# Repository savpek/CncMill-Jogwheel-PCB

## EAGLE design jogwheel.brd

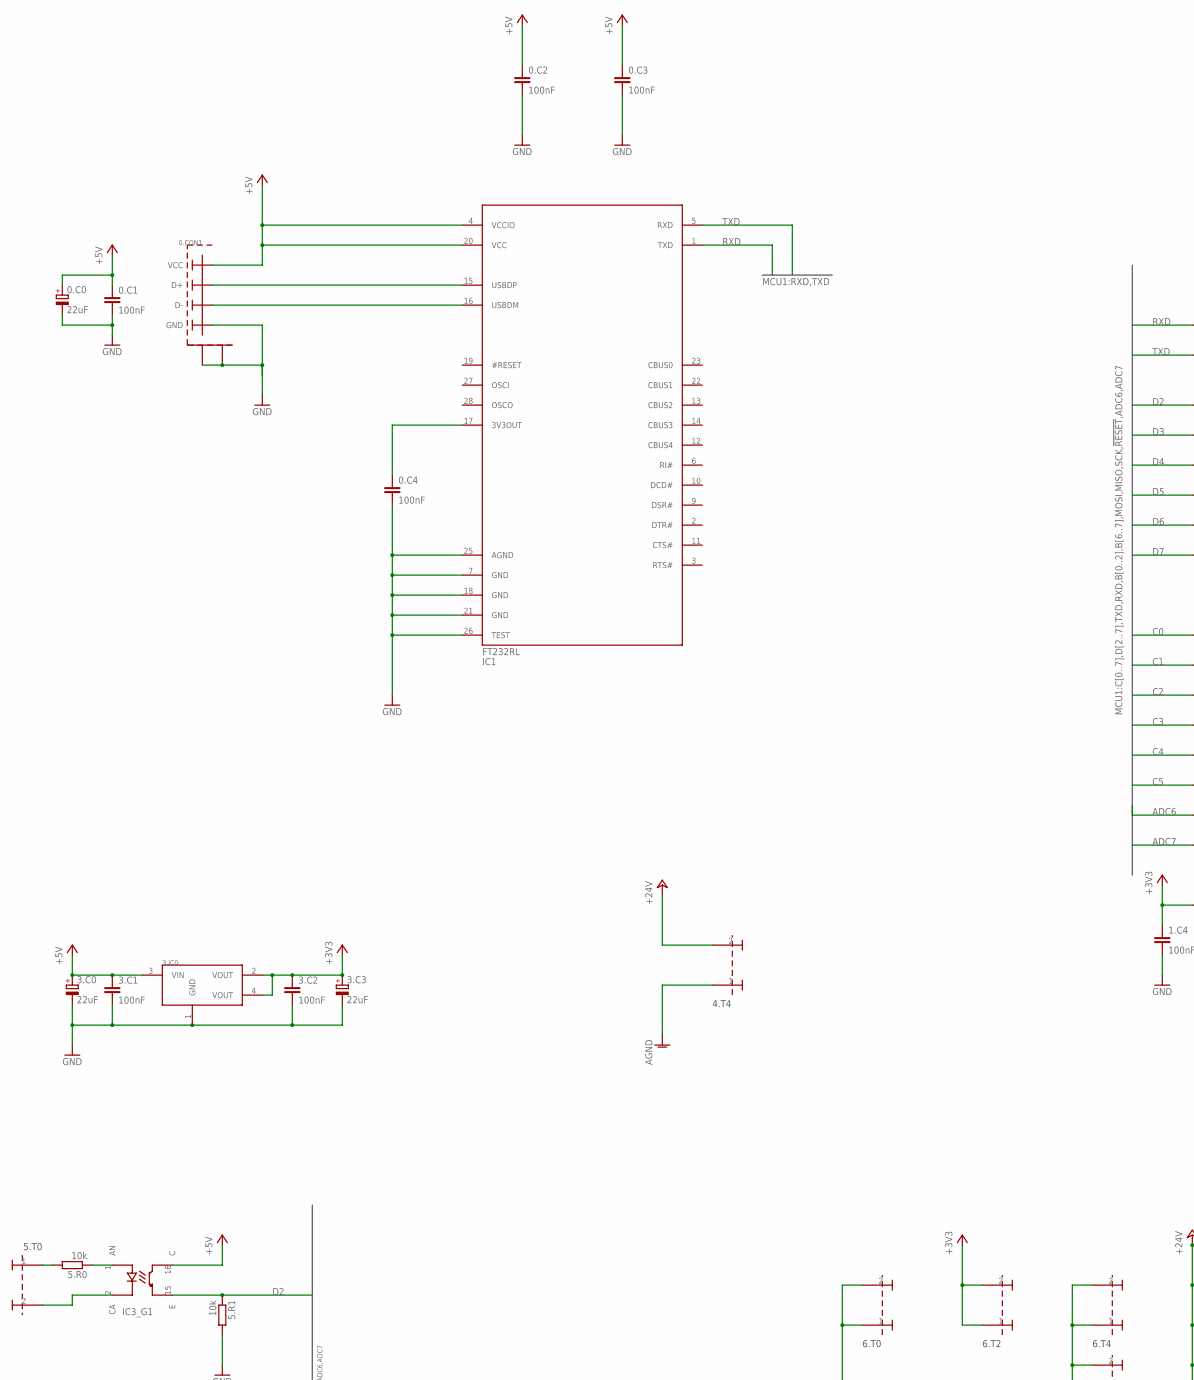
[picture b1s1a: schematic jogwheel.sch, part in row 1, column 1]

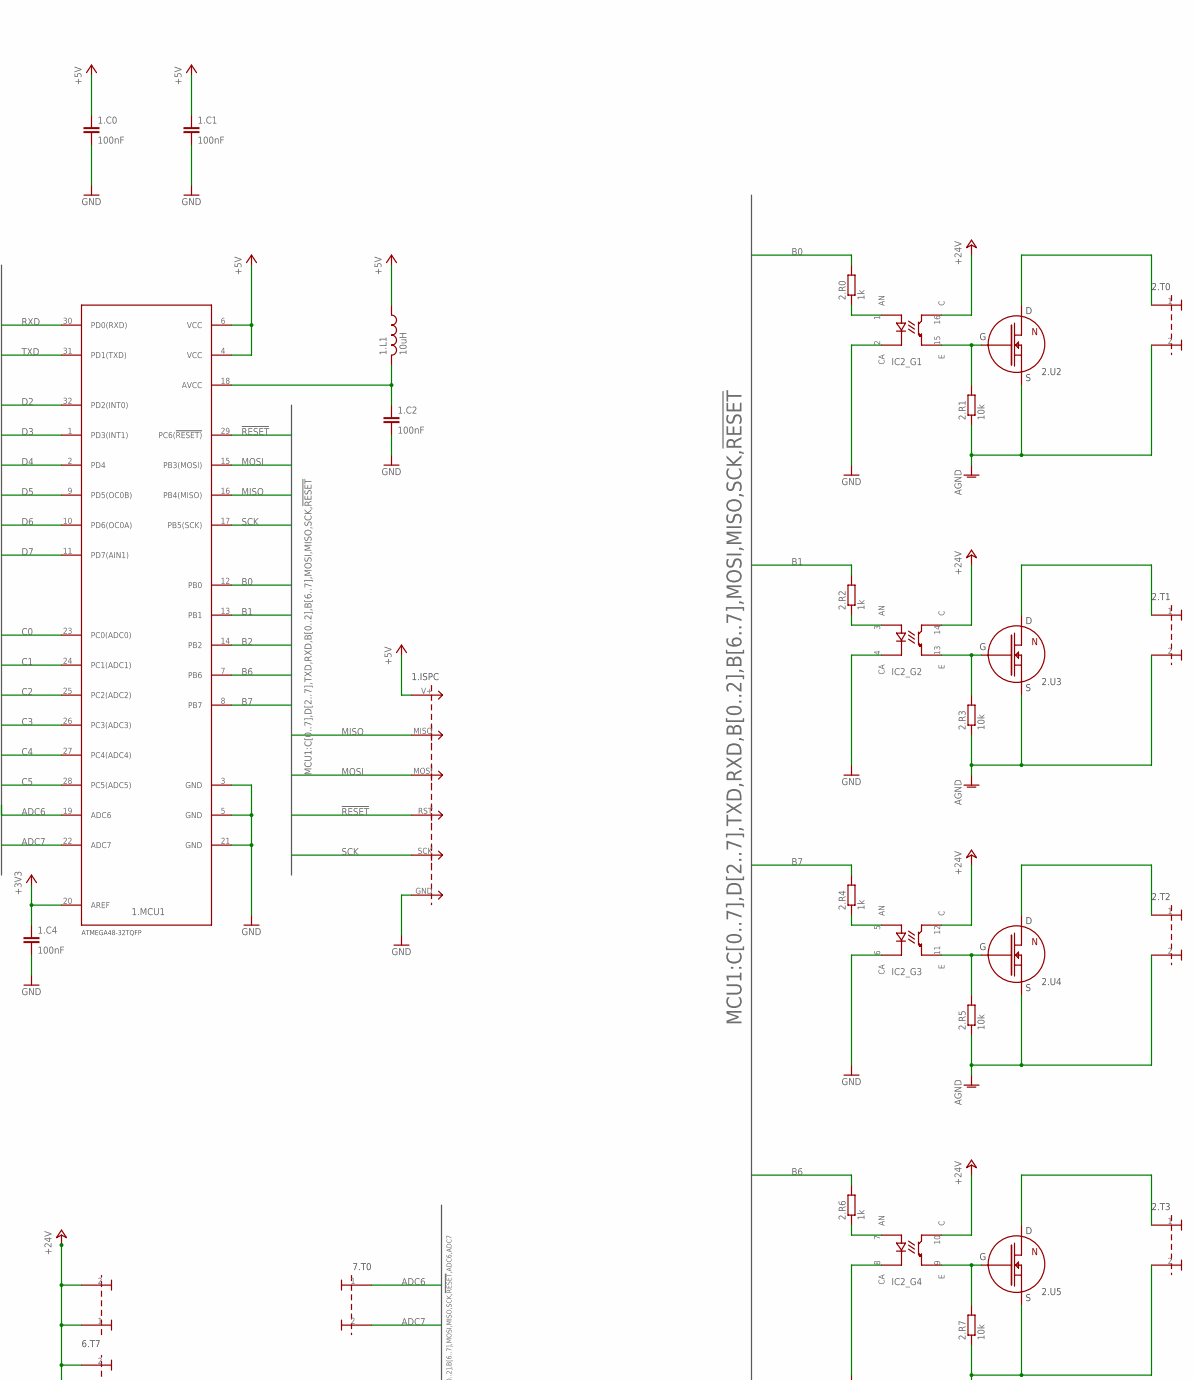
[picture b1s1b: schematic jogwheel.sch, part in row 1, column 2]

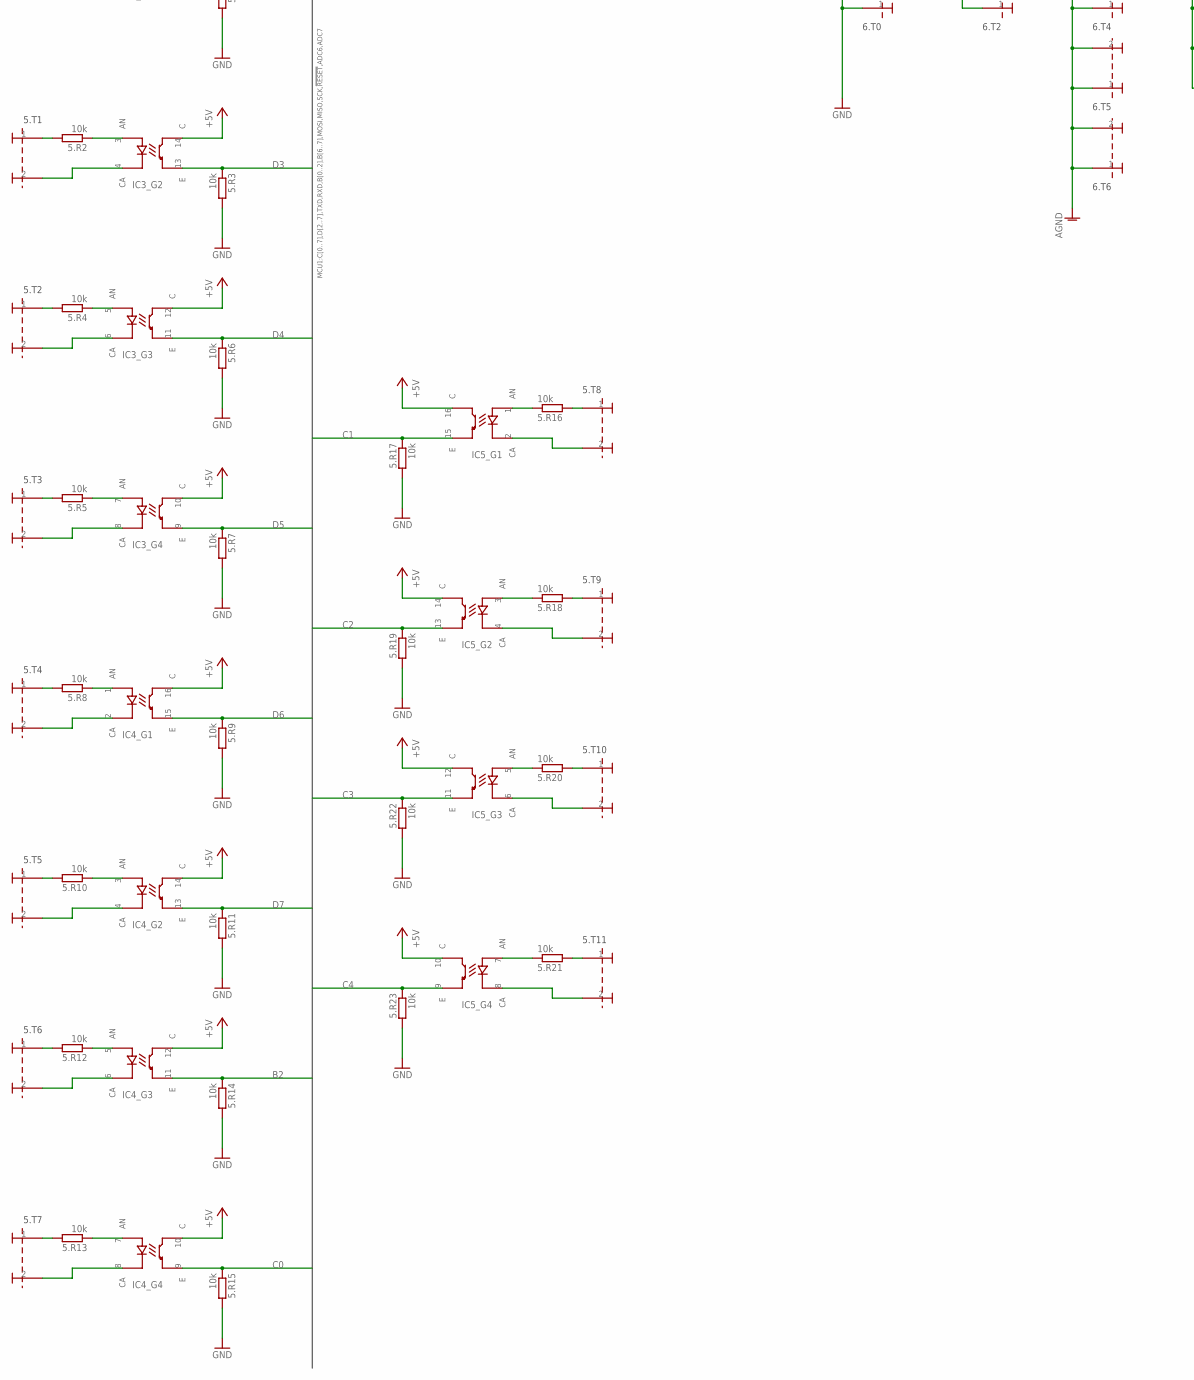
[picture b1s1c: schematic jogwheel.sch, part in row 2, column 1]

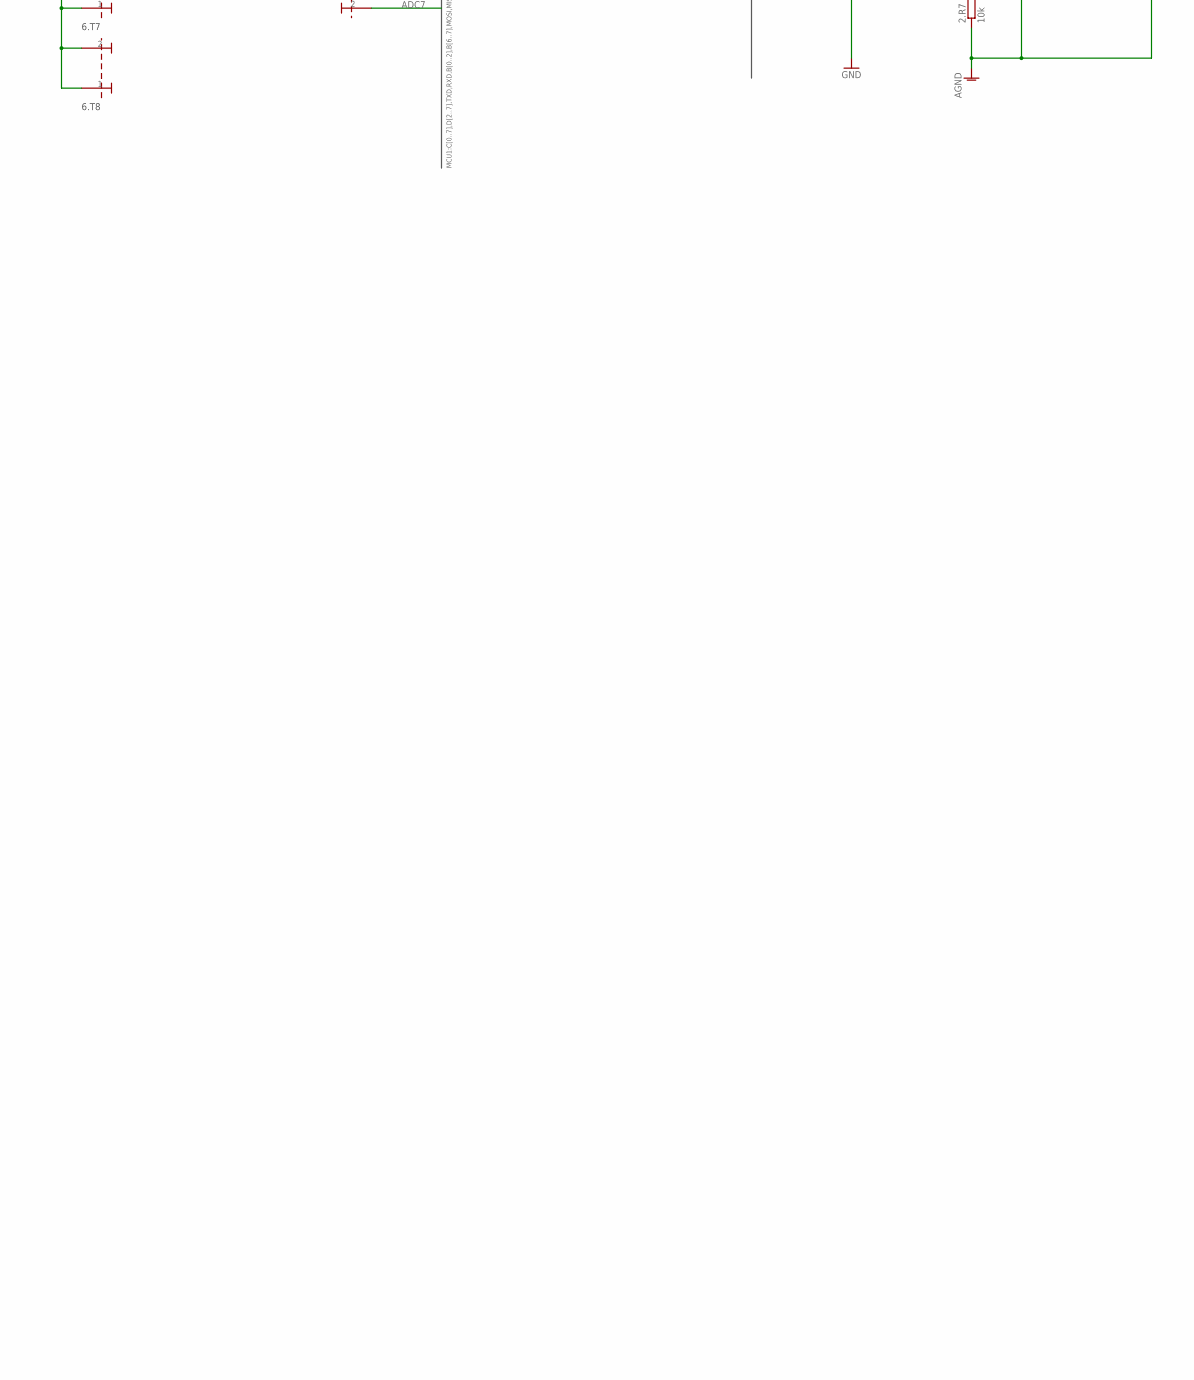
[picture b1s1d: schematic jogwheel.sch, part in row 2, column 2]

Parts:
0.C0, 3.C0, 3.C3: 22uF; E1.5-5
0.C1, 0.C2, 0.C3, 0.C4, 1.C0, 1.C1, 1.C2, 1.C4, 3.C1, 3.C2: 100nF; C0805
0.CON1: USB-BWUERTH-ELECTRONIC-USB-B; USB-B-THROUGH-HOLE
1.ISPC: CONNECTOR_6PIN2X3_ISP; 2X3_ISP
1.L1: 10uH; C0805
1.MCU1: ATMEGA48-20PU-32TQFPTQFP32; TQFP32-08
2.R0, 2.R2, 2.R4, 2.R6: 1k; R0805
2.R1, 2.R3, 2.R5, 2.R7, 5.R0, 5.R1, 5.R2, 5.R3, 5.R4, 5.R5, 5.R6, 5.R7, 5.R8, 5.R9, 5.R10, 5.R11, 5.R12, 5.R13, 5.R14, 5.R15, 5.R16, 5.R17, 5.R18, 5.R19, 5.R20, 5.R21, 5.R22, 5.R23: 10k; R0805
2.T0, 2.T1, 2.T2, 2.T3, 4.T4, 5.T0, 5.T1, 5.T2, 5.T3, 5.T4, 5.T5, 5.T6, 5.T7, 5.T8, 5.T9, 5.T10, 5.T11, 6.T0, 6.T2, 6.T4, 6.T5, 6.T6, 6.T7, 6.T8, 7.T0: CONNECTOR_2PIN2W-TERMINAL-HEADER-20.155MV/2; 2WAY-TERMINAL-HEADER-20.155MV/2
2.U2, 2.U3, 2.U4, 2.U5: N_MOSFET_STD6NF10; STD6NF10
3.IC0: REGULATOR_AP1117E33G-13; SOT223
IC1: FT232RL; SSOP28
IC2, IC3, IC4, IC5: OPTO_4_CHANNELS; ACPL-845-O300

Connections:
!RESET: 1.ISPC.RST, 1.MCU1.29 (PC6(!RESET))
+3V3: 1.C4.1, 1.MCU1.20 (AREF), 3.C2.1, 3.C3.+, 3.IC0.2 (VOUT), 3.IC0.4 (VOUT), 6.T2.1, 6.T2.2
+5V: 0.C0.+, 0.C1.1, 0.C2.1, 0.C3.1, 0.CON1.VCC, 1.C0.1, 1.C1.1, 1.ISPC.V+, 1.L1.1, 1.MCU1.4 (VCC), 1.MCU1.6 (VCC), 3.C0.+, 3.C1.1, 3.IC0.3 (VIN), IC1.4 (VCCIO), IC1.20 (VCC), IC3.10 (C), IC3.12 (C), IC3.14 (C), IC3.16 (C), IC4.10 (C), IC4.12 (C), IC4.14 (C), IC4.16 (C), IC5.10 (C), IC5.12 (C), IC5.14 (C), IC5.16 (C)
+24V: 4.T4.2, 6.T7.1, 6.T7.2, 6.T8.1, 6.T8.2, IC2.10 (C), IC2.12 (C), IC2.14 (C), IC2.16 (C)
ADC6: 1.MCU1.19 (ADC6), 7.T0.1
ADC7: 1.MCU1.22 (ADC7), 7.T0.2
AGND: 2.R1.1, 2.R3.1, 2.R5.1, 2.R7.1, 2.T0.2, 2.T1.2, 2.T2.2, 2.T3.2, 2.U2.3 (S), 2.U3.3 (S), 2.U4.3 (S), 2.U5.3 (S), 4.T4.1, 6.T4.1, 6.T4.2, 6.T5.1, 6.T5.2, 6.T6.1, 6.T6.2
AVCC: 1.C2.1, 1.L1.2, 1.MCU1.18 (AVCC)
B0: 1.MCU1.12 (PB0), 2.R0.2
B1: 1.MCU1.13 (PB1), 2.R2.2
B2: 1.MCU1.14 (PB2), 5.R14.1, IC4.11 (E)
B6: 1.MCU1.7 (PB6), 2.R6.2
B7: 1.MCU1.8 (PB7), 2.R4.2
C0: 1.MCU1.23 (PC0(ADC0)), 5.R15.1, IC4.9 (E)
C1: 1.MCU1.24 (PC1(ADC1)), 5.R17.1, IC5.15 (E)
C2: 1.MCU1.25 (PC2(ADC2)), 5.R19.1, IC5.13 (E)
C3: 1.MCU1.26 (PC3(ADC3)), 5.R22.1, IC5.11 (E)
C4: 1.MCU1.27 (PC4(ADC4)), 5.R23.1, IC5.9 (E)
C5: 1.MCU1.28 (PC5(ADC5))
D2: 1.MCU1.32 (PD2(INT0)), 5.R1.1, IC3.15 (E)
D3: 1.MCU1.1 (PD3(INT1)), 5.R3.1, IC3.13 (E)
D4: 1.MCU1.2 (PD4), 5.R6.1, IC3.11 (E)
D5: 1.MCU1.9 (PD5(OC0B)), 5.R7.1, IC3.9 (E)
D6: 1.MCU1.10 (PD6(OC0A)), 5.R9.1, IC4.15 (E)
D7: 1.MCU1.11 (PD7(AIN1)), 5.R11.1, IC4.13 (E)
GND: 0.C0.-, 0.C1.2, 0.C2.2, 0.C3.2, 0.C4.2, 0.CON1.GND, 0.CON1.SHIELD, 0.CON1.SHIELD@2 (SHIELD), 1.C0.2, 1.C1.2, 1.C2.2, 1.C4.2, 1.ISPC.GND, 1.MCU1.3 (GND), 1.MCU1.5 (GND), 1.MCU1.21 (GND), 3.C0.-, 3.C1.2, 3.C2.2, 3.C3.-, 3.IC0.1 (GND), 5.R1.2, 5.R3.2, 5.R6.2, 5.R7.2, 5.R9.2, 5.R11.2, 5.R14.2, 5.R15.2, 5.R17.2, 5.R19.2, 5.R22.2, 5.R23.2, 6.T0.1, 6.T0.2, IC1.7 (GND), IC1.18 (GND), IC1.21 (GND), IC1.25 (AGND), IC1.26 (TEST), IC2.2 (CA), IC2.4 (CA), IC2.6 (CA), IC2.8 (CA)
MISO: 1.ISPC.MISO, 1.MCU1.16 (PB4(MISO))
MOSI: 1.ISPC.MOSI, 1.MCU1.15 (PB3(MOSI))
unnamed: 2.T2.1, 2.U4.2 (D)
unnamed: 2.T3.1, 2.U5.2 (D)
unnamed: 0.CON1.D+, IC1.15 (USBDP)
unnamed: 0.CON1.D-, IC1.16 (USBDM)
unnamed: 2.R5.2, 2.U4.1 (G), IC2.11 (E)
unnamed: 2.R7.2, 2.U5.1 (G), IC2.9 (E)
unnamed: 0.C4.1, IC1.17 (3V3OUT)
unnamed: 2.T1.1, 2.U3.2 (D)
unnamed: 2.R3.2, 2.U3.1 (G), IC2.13 (E)
unnamed: 2.T0.1, 2.U2.2 (D)
unnamed: 2.R1.2, 2.U2.1 (G), IC2.15 (E)
unnamed: 5.R4.1, IC3.5 (AN)
unnamed: 5.R5.1, IC3.7 (AN)
unnamed: 5.R2.1, IC3.3 (AN)
unnamed: 2.R0.1, IC2.1 (AN)
unnamed: 2.R6.1, IC2.7 (AN)
unnamed: 5.R2.2, 5.T1.1
unnamed: 2.R4.1, IC2.5 (AN)
unnamed: 5.R0.1, IC3.1 (AN)
unnamed: 2.R2.1, IC2.3 (AN)
unnamed: 5.T0.2, IC3.2 (CA)
unnamed: 5.T1.2, IC3.4 (CA)
unnamed: 5.R0.2, 5.T0.1
unnamed: 5.T3.2, IC3.8 (CA)
unnamed: 5.R5.2, 5.T3.1
unnamed: 5.T2.2, IC3.6 (CA)
unnamed: 5.R4.2, 5.T2.1
unnamed: 5.R8.1, IC4.1 (AN)
unnamed: 5.R10.1, IC4.3 (AN)
unnamed: 5.T5.2, IC4.4 (CA)
unnamed: 5.R10.2, 5.T5.1
unnamed: 5.T4.2, IC4.2 (CA)
unnamed: 5.R8.2, 5.T4.1
unnamed: 5.R12.1, IC4.5 (AN)
unnamed: 5.R13.1, IC4.7 (AN)
unnamed: 5.T7.2, IC4.8 (CA)
unnamed: 5.R13.2, 5.T7.1
unnamed: 5.T6.2, IC4.6 (CA)
unnamed: 5.R12.2, 5.T6.1
unnamed: 5.R16.1, IC5.1 (AN)
unnamed: 5.R18.1, IC5.3 (AN)
unnamed: 5.T9.2, IC5.4 (CA)
unnamed: 5.R18.2, 5.T9.1
unnamed: 5.T8.2, IC5.2 (CA)
unnamed: 5.R16.2, 5.T8.1
unnamed: 5.R20.1, IC5.5 (AN)
unnamed: 5.R21.1, IC5.7 (AN)
unnamed: 5.T11.2, IC5.8 (CA)
unnamed: 5.R21.2, 5.T11.1
unnamed: 5.T10.2, IC5.6 (CA)
unnamed: 5.R20.2, 5.T10.1
RXD: 1.MCU1.30 (PD0(RXD)), IC1.1 (TXD)
SCK: 1.ISPC.SCK, 1.MCU1.17 (PB5(SCK))
TXD: 1.MCU1.31 (PD1(TXD)), IC1.5 (RXD)

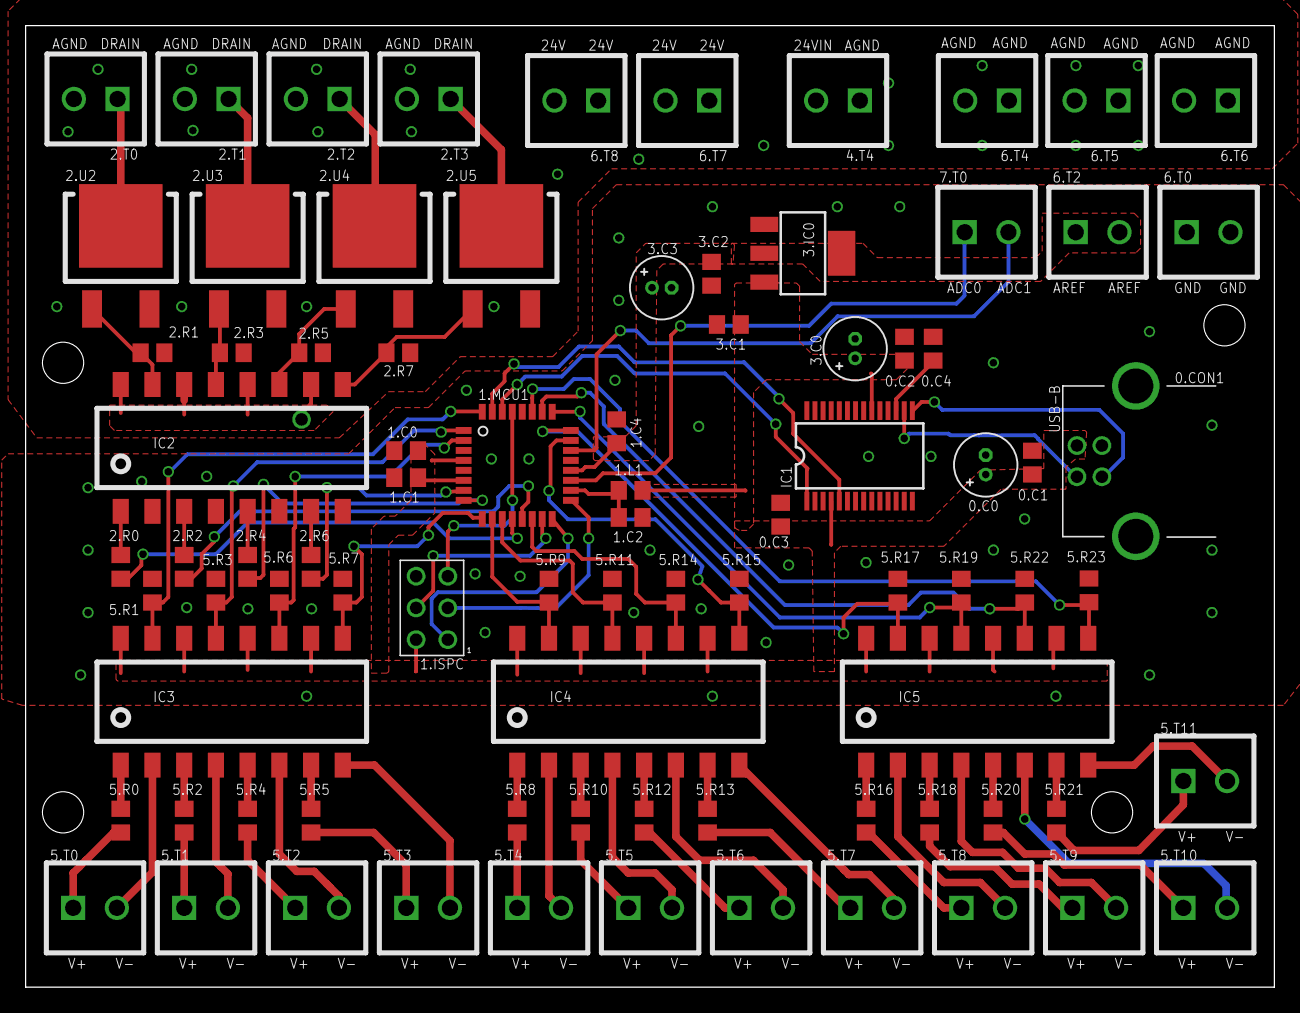
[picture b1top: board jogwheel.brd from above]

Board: 2 copper layers, 100.0 x 77.0 mm, 84 parts (0 on the bottom side), 81 nets.

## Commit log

2012-01-24 Version with 2 way optocouplers.
    Schematic mostly ok. In pcb, core parts (like connectors and ICs)
    are in place.
2012-01-26 Parts in are in correct places (4 line opto version).
    Few traces done. Not many however.
    Fixed silkscreen slightly.
    First version ordered from iteadstudios.
2012-03-21 Fixed usart txd/rxd error from board.
    Accidently, RXD/TXD wasn't crossed...
    Now fixed!
2012-04-17 Added Git-Li.
2012-06-09 Fixed RX/TX in board layout.
2012-07-25 Removed gitli.
